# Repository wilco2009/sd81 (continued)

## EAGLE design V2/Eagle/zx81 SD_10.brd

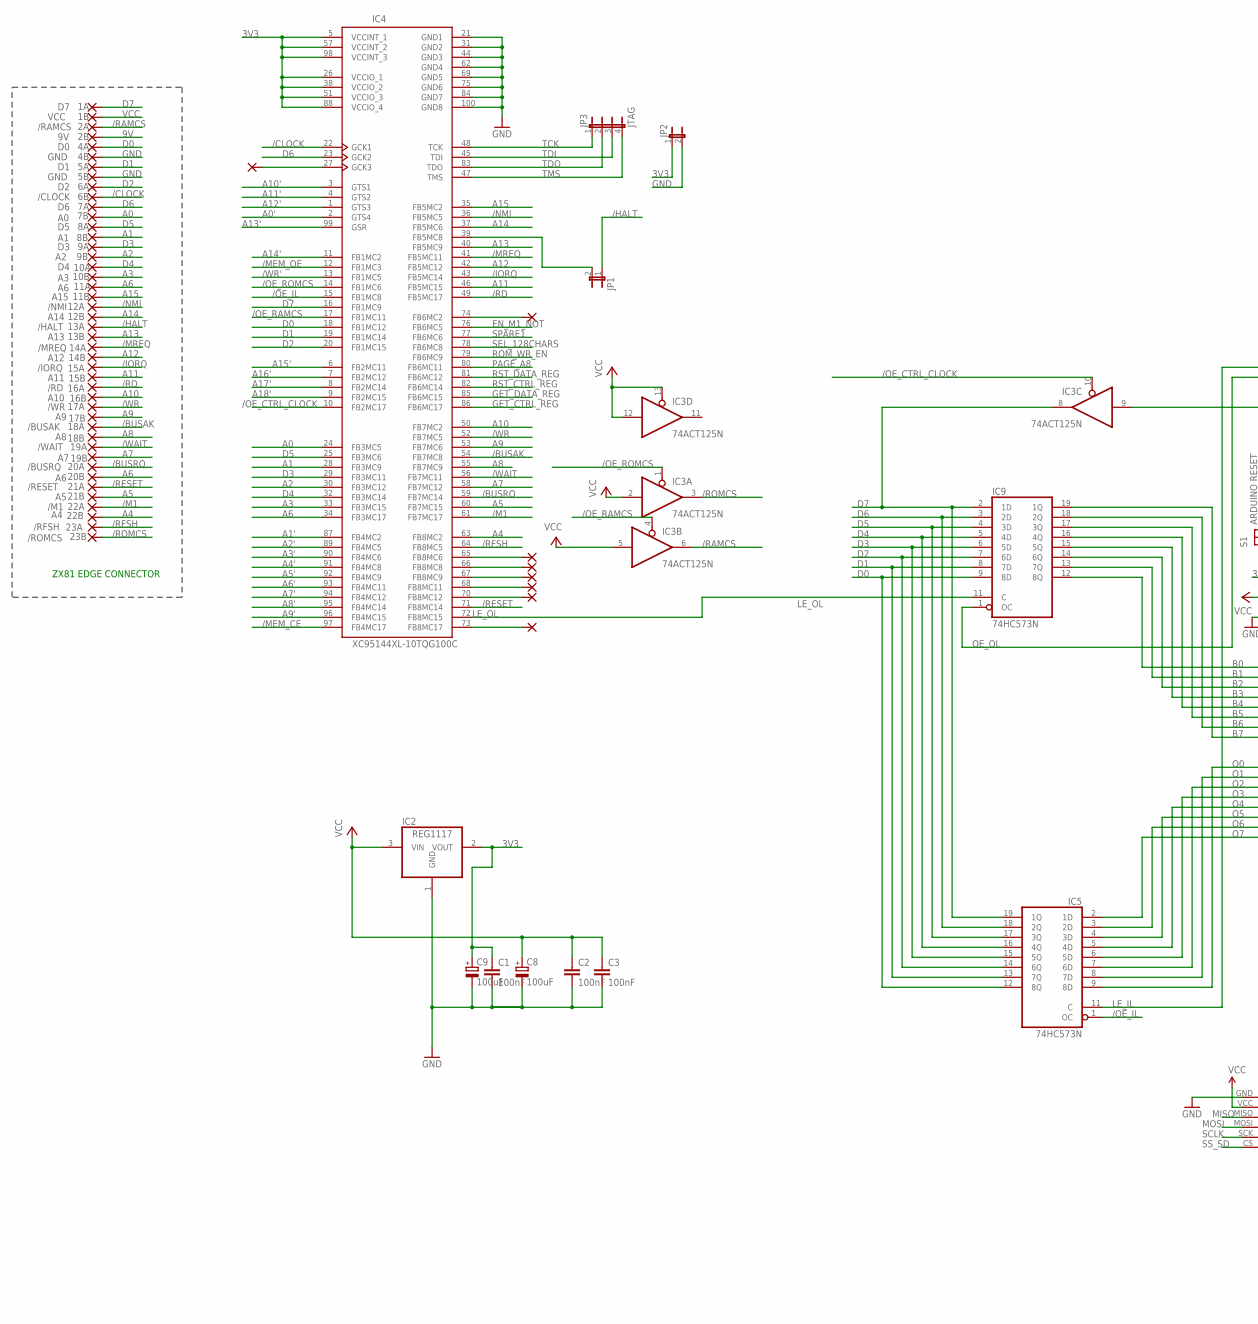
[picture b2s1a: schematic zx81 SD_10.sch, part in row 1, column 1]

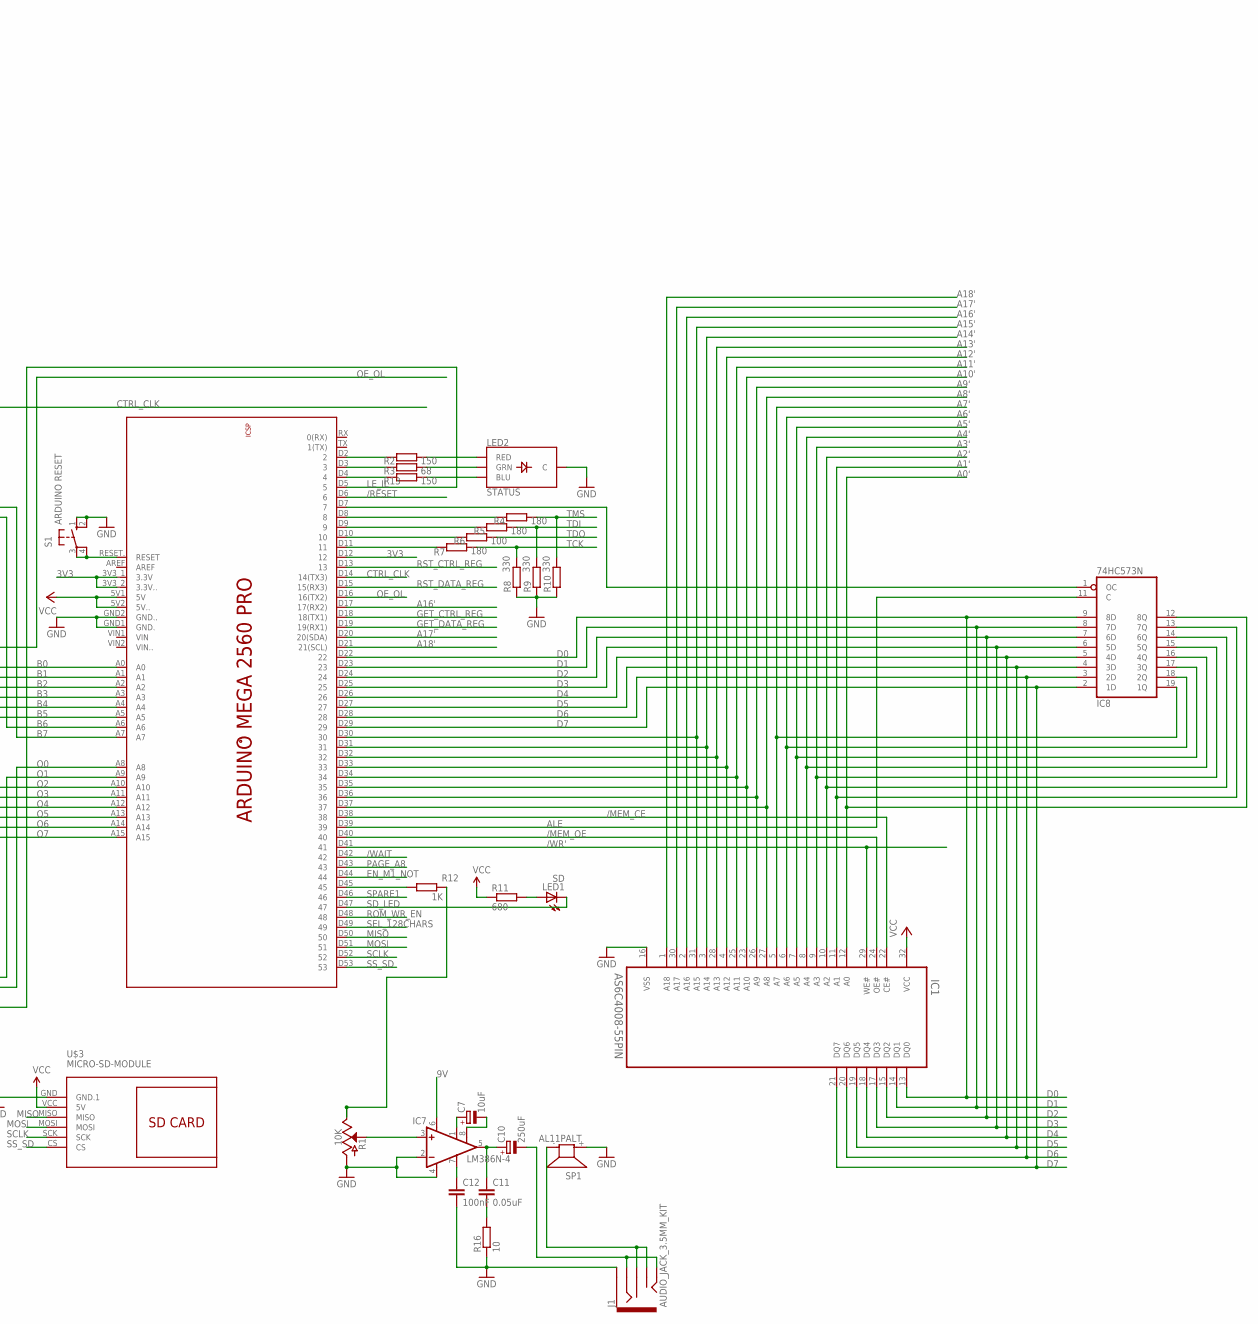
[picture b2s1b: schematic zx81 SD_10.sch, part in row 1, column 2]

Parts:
1A: D7; EDGEPIN
1B: VCC; EDGEPIN
2A: /RAMCS; EDGEPIN
2B: 9V; EDGEPIN
4A: D0; EDGEPIN
4B, 5B: GND; EDGEPIN
5A: D1; EDGEPIN
6A: D2; EDGEPIN
6B: /CLOCK; EDGEPIN
7A: D6; EDGEPIN
7B: A0; EDGEPIN
8A: D5; EDGEPIN
8B: A1; EDGEPIN
9A: D3; EDGEPIN
9B: A2; EDGEPIN
10A: D4; EDGEPIN
10B: A3; EDGEPIN
11A, 20B: A6; EDGEPIN
11B: A15; EDGEPIN
12A: /NMI; EDGEPIN
12B: A14; EDGEPIN
13A: /HALT; EDGEPIN
13B: A13; EDGEPIN
14A: /MREQ; EDGEPIN
14B: A12; EDGEPIN
15A: /IORQ; EDGEPIN
15B: A11; EDGEPIN
16A: /RD; EDGEPIN
16B: A10; EDGEPIN
17A: /WR; EDGEPIN
17B: A9; EDGEPIN
18A: /BUSAK; EDGEPIN
18B: A8; EDGEPIN
19A: /WAIT; EDGEPIN
19B: A7; EDGEPIN
20A: /BUSRQ; EDGEPIN
21A: /RESET; EDGEPIN
21B: A5; EDGEPIN
22A: /M1; EDGEPIN
22B: A4; EDGEPIN
23A: /RFSH; EDGEPIN
23B: /ROMCS; EDGEPIN
C1, C2, C3, C12: 100nF; C025-040X050
C7: 10uF; E2-5
C8, C9: 100uF; E2-5
C10: 250uF; E2-5
C11: 0.05uF; C025-040X050
IC1: AS6C4008-55PIN; DIP1524W45P254L4203H406Q32
IC2: REG1117; SOT223
IC3: 74ACT125N; DIL14
IC4: XC95144XL-10TQG100C; TQFP100
IC5, IC8, IC9: 74HC573N; DIL20
IC7: LM386N-4; DIL08
J1: AUDIO_JACK_3.5MM_KIT; AUDIO-JACK-KIT
JP1, JP2: JP1E; JP1
JP3: JTAG; JP4
LED1: SD; LED5MM
LED2: STATUS; LED-RGB-THRU
PAD1, PAD2, PAD3, PAD4, PAD5, PAD6, PAD7, PAD8: 1,6/0,8
R1: 10K; POT-WHEEL
R2, R13: 150; 0204/7
R3: 68; 0204/7
R4, R5, R7: 180; 0204/7
R6: 100; 0204/7
R8, R9, R10: 330; 0204/7
R11: 680; 0204/7
R12: 1K; 0204/7
R16: 10; 0204/7
S1: ARDUINO RESET; B3F-10XX
SP1: AL11PALT; ALT
U$2: ARDUINO_MEGA2560_PRO
U$3: MICRO-SD-MODULE; MICROSD-MODULE

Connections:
3V3: C1.1, C9.+, IC2.2 (VOUT), IC4.5 (VCCINT_1), IC4.26 (VCCIO_1), IC4.38 (VCCIO_2), IC4.51 (VCCIO_3), IC4.57 (VCCINT_2), IC4.88 (VCCIO_4), IC4.98 (VCCINT_3), JP2.1, U$2.3V3_1 (3.3V), U$2.3V3_2 (3.3V..), U$2.D12 (12)
9V: 2B.1, IC7.6 (VS)
/BUSAK: 18A.1, IC4.54 (FB7MC8)
/BUSRQ: 20A.1, IC4.59 (FB7MC14)
/CLOCK: 6B.1, IC4.22 (GCK1)
/HALT: 13A.1, JP1.1
/IORQ: 15A.1, IC4.43 (FB5MC14)
/M1: 22A.1, IC4.61 (FB7MC17)
/MEM_CE: IC1.22 (CE#), IC4.97 (FB4MC17), U$2.D38 (38)
/MEM_OE: IC1.24 (OE#), IC4.12 (FB1MC3), U$2.D40 (40)
/MREQ: 14A.1, IC4.41 (FB5MC11)
/NMI: 12A.1, IC4.36 (FB5MC5)
/OE_CTRL_CLOCK: IC3.10 (OE), IC4.10 (FB2MC17)
/OE_IL: IC4.15 (FB1MC8), IC5.1 (OC)
/OE_RAMCS: IC3.4 (OE), IC4.17 (FB1MC11)
/OE_ROMCS: IC3.1 (OE), IC4.14 (FB1MC6)
/RAMCS: 2A.1, IC3.6 (O)
/RD: 16A.1, IC4.49 (FB5MC17)
/RESET: 21A.1, IC4.71 (FB8MC14), U$2.D6 (6)
/RFSH: 23A.1, IC4.64 (FB8MC5)
/ROMCS: 23B.1, IC3.3 (O)
/WAIT: 19A.1, IC4.56 (FB7MC11), U$2.D42 (42)
/WR: 17A.1, IC4.52 (FB7MC5)
/WR': IC1.29 (WE#), IC4.13 (FB1MC5), U$2.D41 (41)
A0: 7B.1, IC4.24 (FB3MC5)
A0': IC1.12 (A0), IC4.2 (GTS4), IC8.12 (8Q)
A1: 8B.1, IC4.28 (FB3MC9)
A1': IC1.11 (A1), IC4.87 (FB4MC2), IC8.13 (7Q)
A2: 9B.1, IC4.30 (FB3MC12)
A2': IC1.10 (A2), IC4.89 (FB4MC5), IC8.14 (6Q)
A3: 10B.1, IC4.33 (FB3MC15)
A3': IC1.9 (A3), IC4.90 (FB4MC6), IC8.15 (5Q)
A4: 22B.1, IC4.63 (FB8MC2)
A4': IC1.8 (A4), IC4.91 (FB4MC8), IC8.16 (4Q)
A5: 21B.1, IC4.60 (FB7MC15)
A5': IC1.7 (A5), IC4.92 (FB4MC9), IC8.17 (3Q)
A6: 11A.1, 20B.1, IC4.34 (FB3MC17)
A6': IC1.6 (A6), IC4.93 (FB4MC11), IC8.18 (2Q)
A7: 19B.1, IC4.58 (FB7MC12)
A7': IC1.5 (A7), IC4.94 (FB4MC12), IC8.19 (1Q)
A8: 18B.1, IC4.55 (FB7MC9)
A8': IC1.27 (A8), IC4.95 (FB4MC14), U$2.D37 (37)
A9: 17B.1, IC4.53 (FB7MC6)
A9': IC1.26 (A9), IC4.96 (FB4MC15), U$2.D36 (36)
A10: 16B.1, IC4.50 (FB7MC2)
A10': IC1.23 (A10), IC4.3 (GTS1), U$2.D35 (35)
A11: 15B.1, IC4.46 (FB5MC15)
A11': IC1.25 (A11), IC4.4 (GTS2), U$2.D34 (34)
A12: 14B.1, IC4.42 (FB5MC12)
A12': IC1.4 (A12), IC4.1 (GTS3), U$2.D33 (33)
A13: 13B.1, IC4.40 (FB5MC9)
A13': IC1.28 (A13), IC4.99 (GSR), U$2.D32 (32)
A14: 12B.1, IC4.37 (FB5MC6)
A14': IC1.3 (A14), IC4.11 (FB1MC2), U$2.D31 (31)
A15: 11B.1, IC4.35 (FB5MC2)
A15': IC1.31 (A15), IC4.6 (FB2MC11), U$2.D30 (30)
A16': IC1.2 (A16), IC4.7 (FB2MC12), U$2.D17 (17(RX2))
A17': IC1.30 (A17), IC4.8 (FB2MC14), U$2.D20 (20(SDA))
A18': IC1.1 (A18), IC4.9 (FB2MC15), U$2.D21 (21(SCL))
ALE: IC8.11 (C), U$2.D39 (39)
B0: IC9.19 (1Q), U$2.A7
B1: IC9.18 (2Q), U$2.A6
B2: IC9.17 (3Q), U$2.A5
B3: IC9.16 (4Q), U$2.A4
B4: IC9.15 (5Q), U$2.A3
B5: IC9.14 (6Q), U$2.A2
B6: IC9.13 (7Q), U$2.A1
B7: IC9.12 (8Q), U$2.A0
CTRL_CLK: IC3.9 (I), U$2.D14 (14(TX3))
D0: 4A.1, IC1.13 (DQ0), IC4.18 (FB1MC12), IC5.12 (8Q), IC8.9 (8D), IC9.9 (8D), U$2.D22 (22)
D1: 5A.1, IC1.14 (DQ1), IC4.19 (FB1MC14), IC5.13 (7Q), IC8.8 (7D), IC9.8 (7D), U$2.D23 (23)
D2: 6A.1, IC1.15 (DQ2), IC4.20 (FB1MC15), IC5.14 (6Q), IC8.7 (6D), IC9.7 (6D), U$2.D24 (24)
D3: 9A.1, IC1.17 (DQ3), IC4.29 (FB3MC11), IC5.15 (5Q), IC8.6 (5D), IC9.6 (5D), U$2.D25 (25)
D4: 10A.1, IC1.18 (DQ4), IC4.32 (FB3MC14), IC5.16 (4Q), IC8.5 (4D), IC9.5 (4D), U$2.D26 (26)
D5: 8A.1, IC1.19 (DQ5), IC4.25 (FB3MC6), IC5.17 (3Q), IC8.4 (3D), IC9.4 (3D), U$2.D27 (27)
D6: 7A.1, IC1.20 (DQ6), IC4.23 (GCK2), IC5.18 (2Q), IC8.3 (2D), IC9.3 (2D), U$2.D28 (28)
D7: 1A.1, IC1.21 (DQ7), IC3.8 (O), IC4.16 (FB1MC9), IC5.19 (1Q), IC8.2 (1D), IC9.2 (1D), U$2.D29 (29)
EN_M1_NOT: IC4.76 (FB6MC5), U$2.D44 (44)
GET_CTRL_REG: IC4.86 (FB6MC17), U$2.D18 (18(TX1))
GET_DATA_REG: IC4.85 (FB6MC15), U$2.D19 (19(RX1))
GND: 4B.1, 5B.1, C1.2, C2.2, C3.2, C8.-, C9.-, C12.2, IC1.16 (VSS), IC2.1 (GND), IC3.7 (GND), IC4.21 (GND1), IC4.31 (GND2), IC4.44 (GND3), IC4.62 (GND4), IC4.69 (GND5), IC4.75 (GND6), IC4.84 (GND7), IC4.100 (GND8), IC5.10 (GND), IC7.2 (-IN), IC7.4 (GND), IC8.10 (GND), IC9.10 (GND), J1.SLEEVE, JP2.2, LED2.2 (C), R1.P$1 (A), R8.1, R9.1, R10.1, R16.1, S1.1 (S), S1.2 (S1), SP1.+ (1), U$2.GND1 (GND.), U$2.GND2 (GND..), U$3.GND (GND.1)
LE_IL: IC5.11 (C), U$2.D5 (5)
LE_OL: IC4.72 (FB8MC15), IC9.11 (C)
MISO: U$2.D50 (50), U$3.MISO
MOSI: U$2.D51 (51), U$3.MOSI
unnamed: IC8.1 (OC), U$2.D7 (7)
unnamed: IC4.74 (FB6MC2), PAD8.1
unnamed: J1.RSH, J1.TSH, SP1.- (2)
unnamed: R4.1, U$2.D8 (8)
unnamed: C10.-, J1.RING, J1.TIP
unnamed: IC7.3 (+IN), R1.P$3 (S)
unnamed: R1.P$2 (E), R12.2
unnamed: R12.1, U$2.D45 (45)
unnamed: C7.+, IC7.1 (GAIN)
unnamed: IC4.65 (FB8MC6), PAD2.1
unnamed: R5.1, U$2.D9 (9)
unnamed: R6.1, U$2.D10 (10)
unnamed: R7.1, U$2.D11 (11)
unnamed: LED1.A, R11.2
unnamed: IC4.66 (FB8MC8), PAD3.1
unnamed: C7.-, IC7.8 (GAIN)
unnamed: C10.+, C11.1, IC7.5 (OUT)
unnamed: IC4.67 (FB8MC9), PAD4.1
unnamed: C12.1, IC7.7 (BYPASS)
unnamed: C11.2, R16.2
unnamed: IC4.68 (FB8MC11), PAD5.1
unnamed: IC4.73 (FB8MC17), PAD6.1
unnamed: IC4.27 (GCK3), PAD1.1
unnamed: IC4.70 (FB8MC12), PAD7.1
unnamed: LED2.1 (RED), R2.2
unnamed: LED2.4 (GRN), R3.2
unnamed: LED2.3 (BLU), R13.2
unnamed: R2.1, U$2.D2 (2)
unnamed: R3.1, U$2.D3 (3)
unnamed: R13.1, U$2.D4 (4)
unnamed: S1.3, S1.4 (P1), U$2.RESET. (RESET)
unnamed: IC4.39 (FB5MC8), JP1.2
O0: IC5.2 (1D), U$2.A15
O1: IC5.3 (2D), U$2.A14
O2: IC5.4 (3D), U$2.A13
O3: IC5.5 (4D), U$2.A12
O4: IC5.6 (5D), U$2.A11
O5: IC5.7 (6D), U$2.A10
O6: IC5.8 (7D), U$2.A9
O7: IC5.9 (8D), U$2.A8
OE_OL: IC9.1 (OC), U$2.D16 (16(TX2))
PAGE_A8: IC4.80 (FB6MC11), U$2.D43 (43)
ROM_WR_EN: IC4.79 (FB6MC9), U$2.D48 (48)
RST_CTRL_REG: IC4.82 (FB6MC14), U$2.D13 (13)
RST_DATA_REG: IC4.81 (FB6MC12), U$2.D15 (15(RX3))
SCLK: U$2.D52 (52), U$3.SCK
SD_LED: LED1.K (C), U$2.D47 (47)
SEL_128CHARS: IC4.78 (FB6MC8), U$2.D49 (49)
SPARE1: IC4.77 (FB6MC6), U$2.D46 (46)
SS_SD: U$2.D53 (53), U$3.CS
TCK: IC4.48 (TCK), JP3.1, R7.2, R8.2
TDI: IC4.45 (TDI), JP3.3, R5.2, R9.2
TDO: IC4.83 (TDO), JP3.2, R6.2
TMS: IC4.47 (TMS), JP3.4, R4.2, R10.2
VCC: 1B.1, C2.1, C3.1, C8.+, IC1.32 (VCC), IC2.3 (VIN), IC3.2 (I), IC3.5 (I), IC3.12 (I), IC3.13 (OE), IC3.14 (VCC), IC5.20 (VCC), IC8.20 (VCC), IC9.20 (VCC), R11.1, U$2.5V1 (5V), U$2.5V2 (5V..), U$3.VCC (5V)

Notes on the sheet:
ZX81 EDGE CONNECTOR

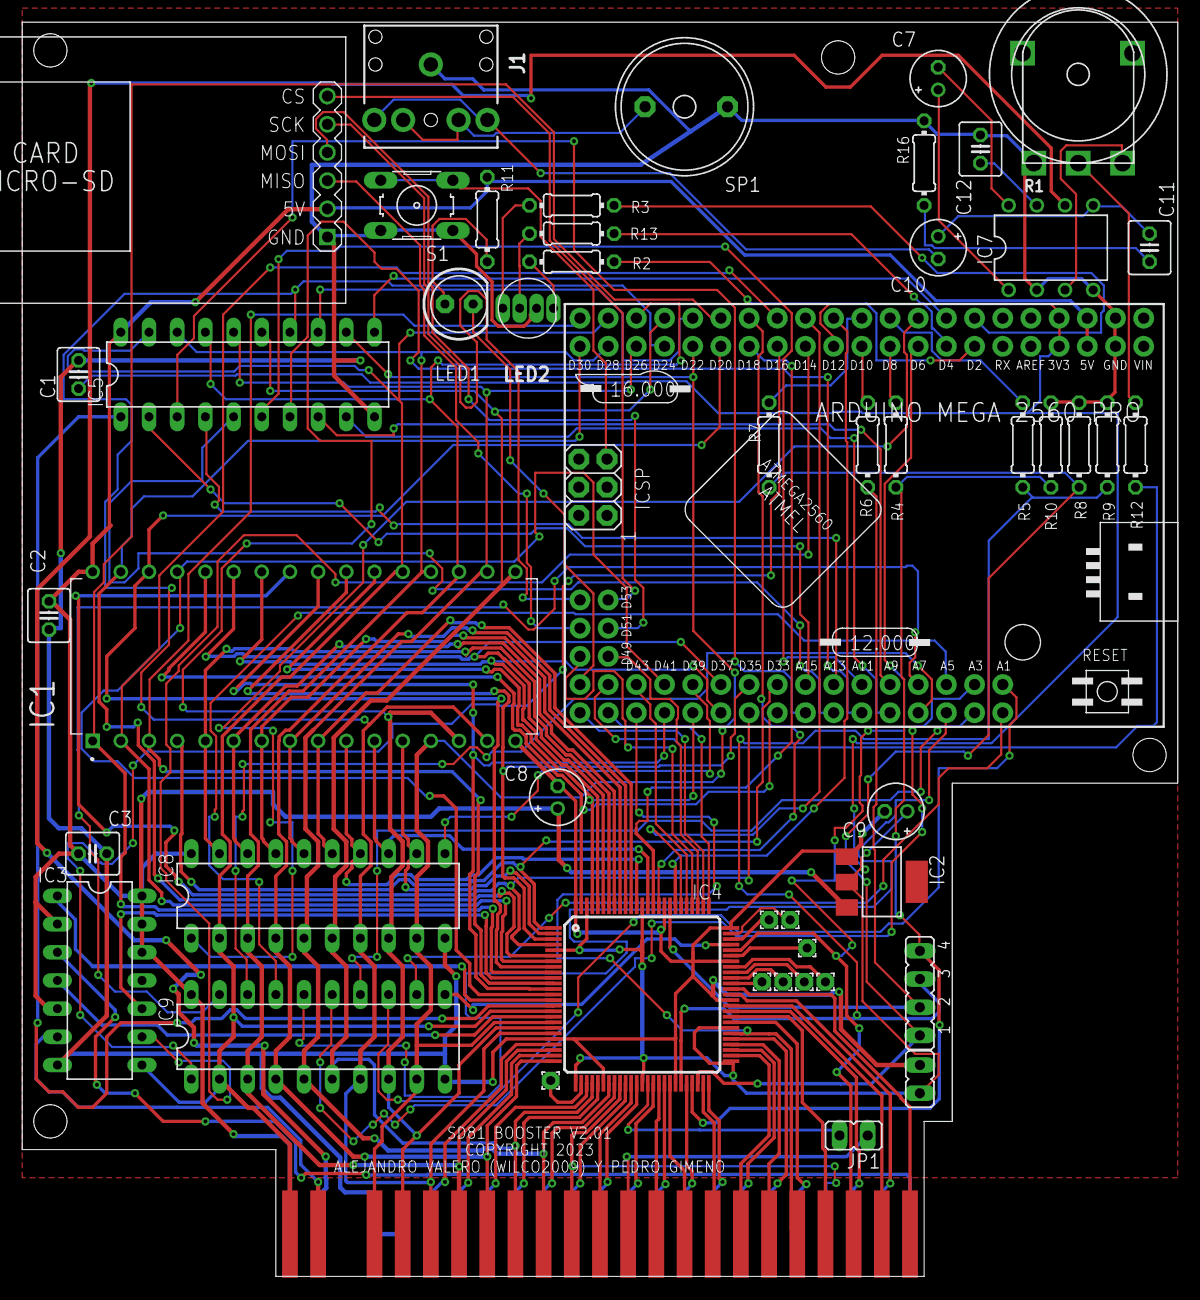
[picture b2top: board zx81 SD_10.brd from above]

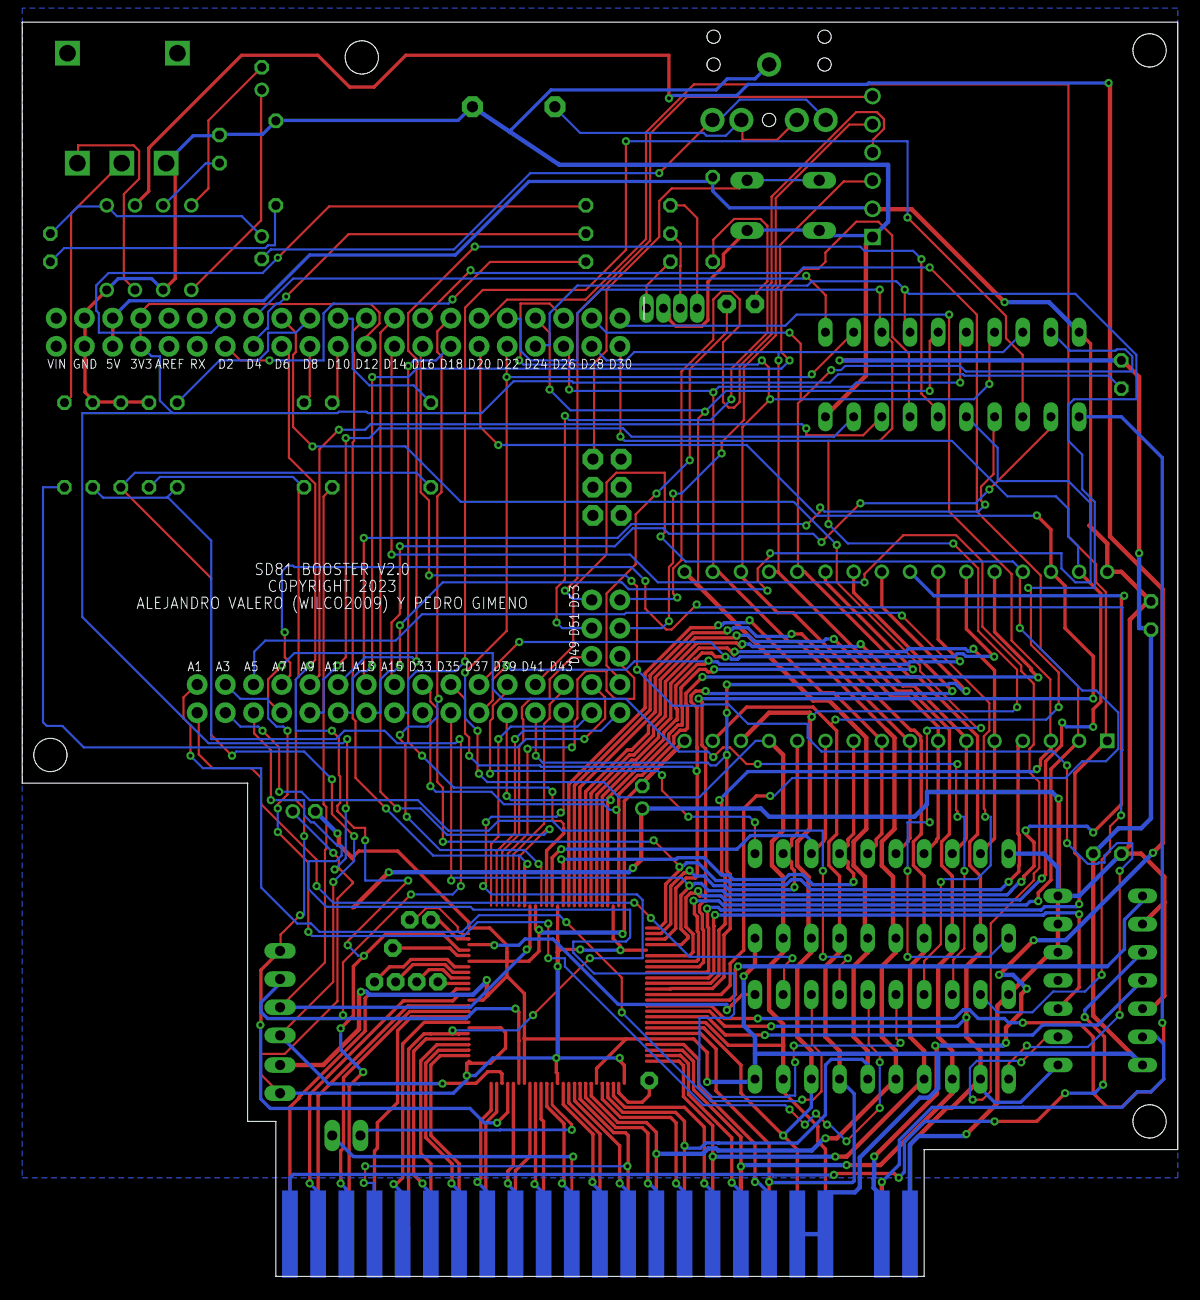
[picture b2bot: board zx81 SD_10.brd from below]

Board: 2 copper layers, 104.1 x 113.0 mm, 93 parts (22 on the bottom side), 140 nets.

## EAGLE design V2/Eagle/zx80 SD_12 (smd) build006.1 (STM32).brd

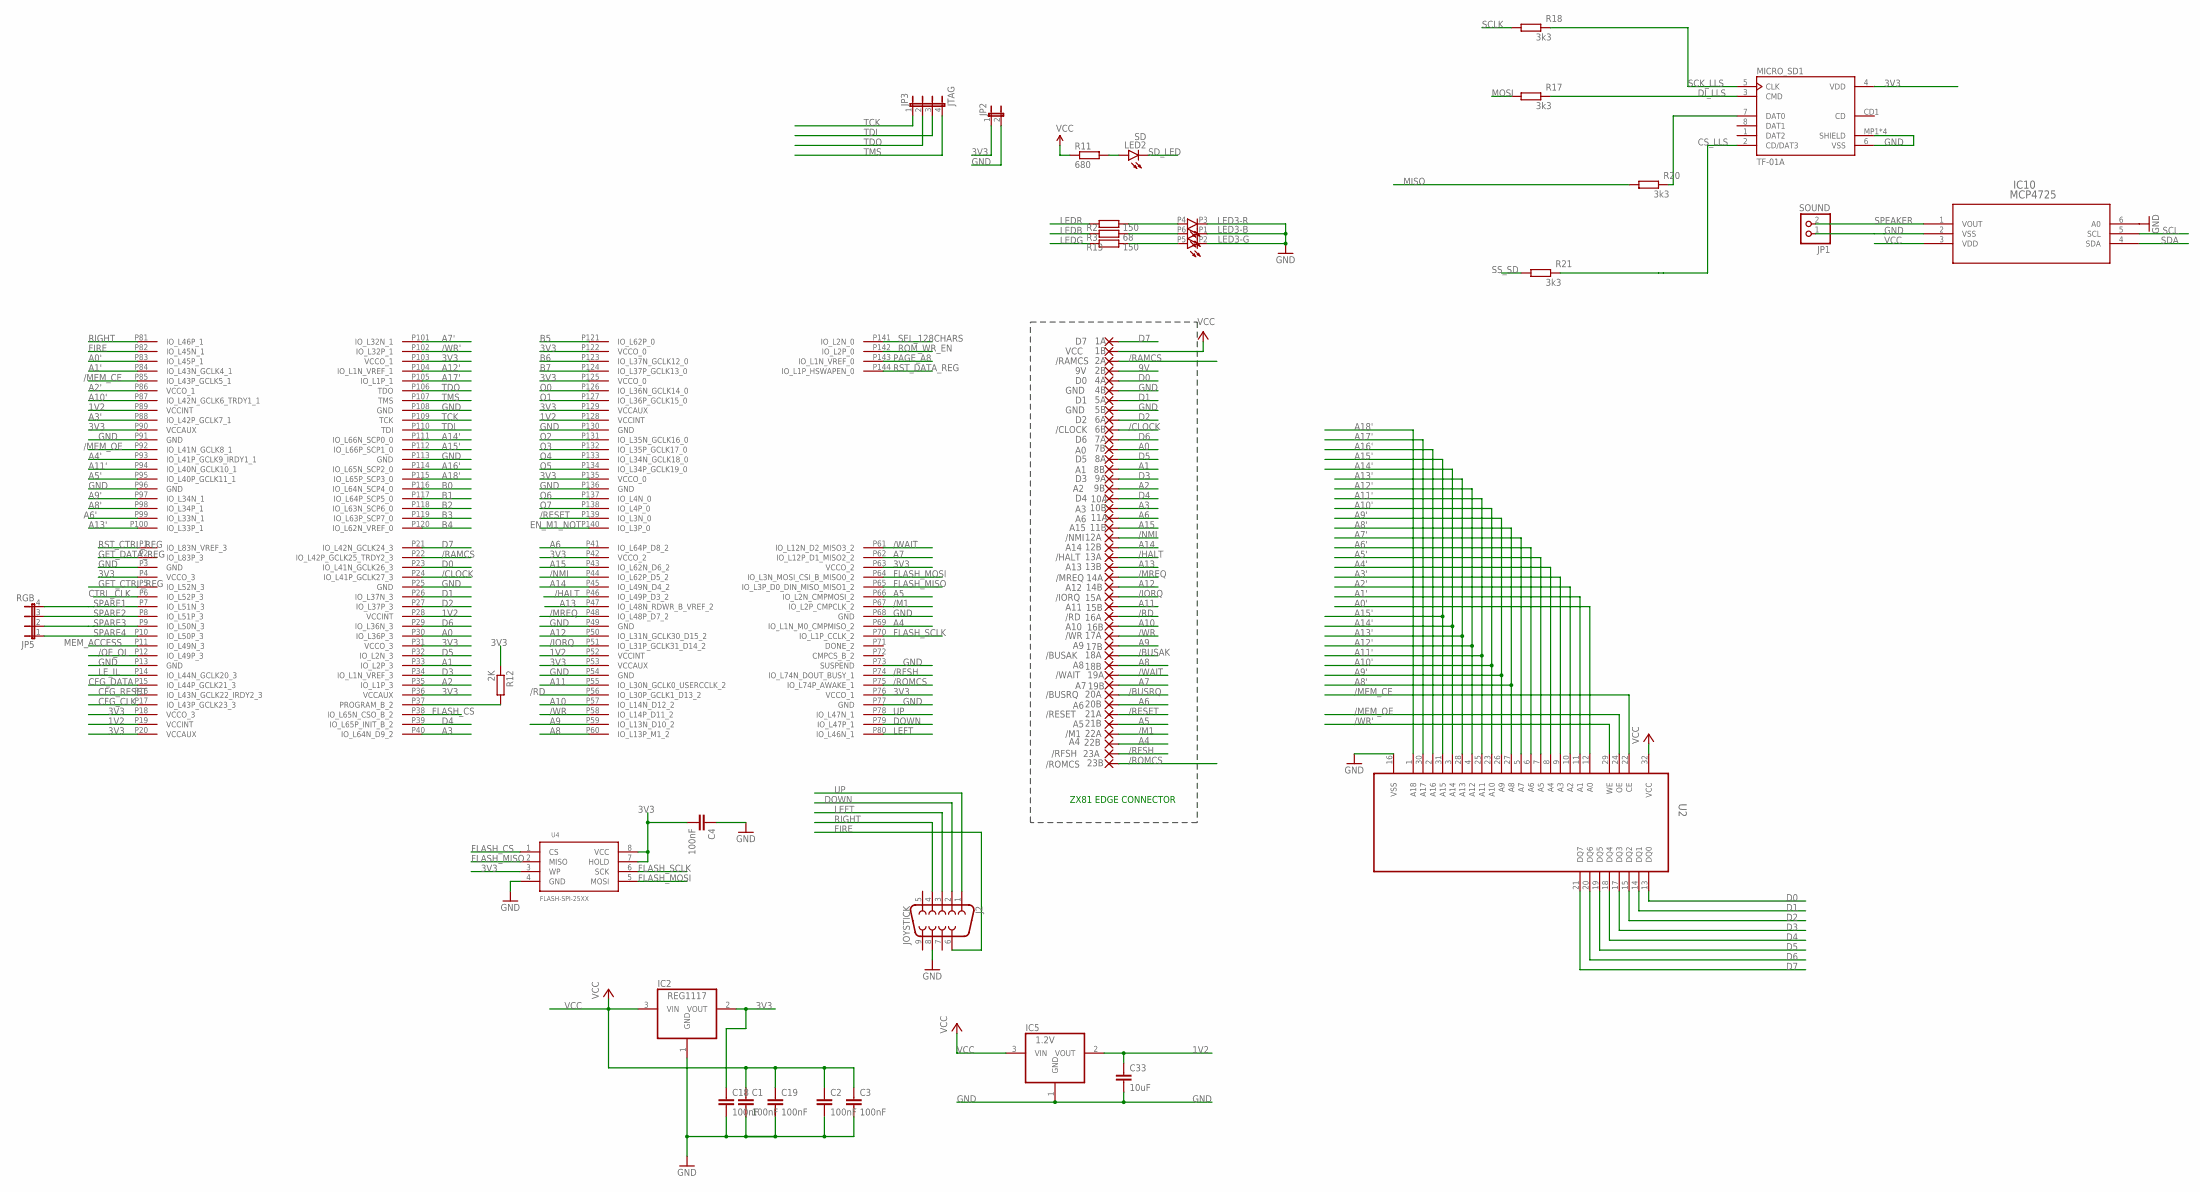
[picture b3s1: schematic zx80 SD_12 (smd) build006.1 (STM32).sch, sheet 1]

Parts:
1A: D7; EDGEPIN
1B: VCC; EDGEPIN
2A: /RAMCS; EDGEPIN
2B: 9V; EDGEPIN
4A: D0; EDGEPIN
4B, 5B: GND; EDGEPIN
5A: D1; EDGEPIN
6A: D2; EDGEPIN
6B: /CLOCK; EDGEPIN
7A: D6; EDGEPIN
7B: A0; EDGEPIN
8A: D5; EDGEPIN
8B: A1; EDGEPIN
9A: D3; EDGEPIN
9B: A2; EDGEPIN
10A: D4; EDGEPIN
10B: A3; EDGEPIN
11A, 20B: A6; EDGEPIN
11B: A15; EDGEPIN
12A: /NMI; EDGEPIN
12B: A14; EDGEPIN
13A: /HALT; EDGEPIN
13B: A13; EDGEPIN
14A: /MREQ; EDGEPIN
14B: A12; EDGEPIN
15A: /IORQ; EDGEPIN
15B: A11; EDGEPIN
16A: /RD; EDGEPIN
16B: A10; EDGEPIN
17A: /WR; EDGEPIN
17B: A9; EDGEPIN
18A: /BUSAK; EDGEPIN
18B: A8; EDGEPIN
19A: /WAIT; EDGEPIN
19B: A7; EDGEPIN
20A: /BUSRQ; EDGEPIN
21A: /RESET; EDGEPIN
21B: A5; EDGEPIN
22A: /M1; EDGEPIN
22B: A4; EDGEPIN
23A: /RFSH; EDGEPIN
23B: /ROMCS; EDGEPIN
C1, C2, C3, C18, C19: 100nF; C0603
C4: 100nF; C0603K
C33: 10uF; C0603K
IC2: REG1117; SOT223
IC5: 1.2V; SOT223
IC10: MCP4725; SOT-23-6_MC
J2: JOYSTICK; DB9_MALE
JP1: SOUND; 1X02
JP2: JP1E; JP1
JP3: JTAG; JP4
JP5: RGB; JP4
LED2: SD; CHIPLED_0603
LED3: STATUS; 3535-PLCC6
MICRO_SD1: TF-01A
R2, R13: 150; R0603
R3: 68; R0603
R11: 680; R0603
R12: 2K; R0603
R17, R18, R20, R21: 3k3; R0603
U2: AS6C4008; SOP32-5
U4: FLASH-SPI-25XX; SO08-EIAJ
U$1: XC6SLX9-2TQG144C; TQ144

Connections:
1V2: C33.1, IC5.2 (VOUT), U$1.P19 (VCCINT), U$1.P28 (VCCINT), U$1.P52 (VCCINT), U$1.P89 (VCCINT), U$1.P128 (VCCINT)
3V3: C4.2, C18.1, IC2.2 (VOUT), JP2.1, MICRO_SD1.4 (VDD), R12.1, U4.3 (WP), U4.7 (HOLD), U4.8 (VCC), U$1.P4 (VCCO_3), U$1.P18 (VCCO_3), U$1.P20 (VCCAUX), U$1.P31 (VCCO_3), U$1.P36 (VCCAUX), U$1.P42 (VCCO_2), U$1.P53 (VCCAUX), U$1.P63 (VCCO_2), U$1.P76 (VCCO_1), U$1.P90 (VCCAUX), U$1.P103 (VCCO_1), U$1.P122 (VCCO_0), U$1.P125 (VCCO_0), U$1.P129 (VCCAUX), U$1.P135 (VCCO_0); also elsewhere on the board
9V: 2B.1
/BUSAK: 18A.1
/BUSRQ: 20A.1
/CLOCK: 6B.1, U$1.P24 (IO_L41P_GCLK27_3)
/HALT: 13A.1, U$1.P46 (IO_L49P_D3_2)
/IORQ: 15A.1, U$1.P51 (IO_L31P_GCLK31_D14_2)
/M1: 22A.1, U$1.P67 (IO_L2P_CMPCLK_2)
/MEM_CE: U2.22 (CE), U$1.P85 (IO_L43P_GCLK5_1)
/MEM_OE: U2.24 (OE), U$1.P92 (IO_L41N_GCLK8_1)
/MREQ: 14A.1, U$1.P48 (IO_L48P_D7_2)
/NMI: 12A.1, U$1.P44 (IO_L62P_D5_2)
/OE_OL: U$1.P12 (IO_L49P_3); also elsewhere on the board
/RAMCS: 2A.1, U$1.P22 (IO_L42P_GCLK25_TRDY2_3)
/RD: 16A.1, U$1.P56 (IO_L30P_GCLK1_D13_2)
/RESET: 21A.1, U$1.P139 (IO_L3N_0); also elsewhere on the board
/RFSH: 23A.1, U$1.P74 (IO_L74N_DOUT_BUSY_1)
/ROMCS: 23B.1, U$1.P75 (IO_L74P_AWAKE_1)
/WAIT: 19A.1, U$1.P61 (IO_L12N_D2_MISO3_2); also elsewhere on the board
/WR: 17A.1, U$1.P58 (IO_L14P_D11_2); also elsewhere on the board
/WR': U2.29 (WE), U$1.P102 (IO_L32P_1)
A0: 7B.1, U$1.P30 (IO_L36P_3)
A0': U2.12 (A0), U$1.P83 (IO_L45P_1); also elsewhere on the board
A1: 8B.1, U$1.P33 (IO_L2P_3)
A1': U2.11 (A1), U$1.P84 (IO_L43N_GCLK4_1); also elsewhere on the board
A2: 9B.1, U$1.P35 (IO_L1P_3)
A2': U2.10 (A2), U$1.P86 (VCCO_1); also elsewhere on the board
A3: 10B.1, U$1.P40 (IO_L64N_D9_2)
A3': U2.9 (A3), U$1.P88 (IO_L42P_GCLK7_1); also elsewhere on the board
A4: 22B.1, U$1.P69 (IO_L1N_M0_CMPMISO_2)
A4': U2.8 (A4), U$1.P93 (IO_L41P_GCLK9_IRDY1_1); also elsewhere on the board
A5: 21B.1, U$1.P66 (IO_L2N_CMPMOSI_2)
A5': U2.7 (A5), U$1.P95 (IO_L40P_GCLK11_1); also elsewhere on the board
A6: 11A.1, 20B.1, U$1.P41 (IO_L64P_D8_2)
A6': U2.6 (A6), U$1.P99 (IO_L33N_1); also elsewhere on the board
A7: 19B.1, U$1.P62 (IO_L12P_D1_MISO2_2)
A7': U2.5 (A7), U$1.P101 (IO_L32N_1); also elsewhere on the board
A8: 18B.1, U$1.P60 (IO_L13P_M1_2)
A8': U2.27 (A8), U$1.P98 (IO_L34P_1); also elsewhere on the board
A9: 17B.1, U$1.P59 (IO_L13N_D10_2)
A9': U2.26 (A9), U$1.P97 (IO_L34N_1); also elsewhere on the board
A10: 16B.1, U$1.P57 (IO_L14N_D12_2)
A10': U2.23 (A10), U$1.P87 (IO_L42N_GCLK6_TRDY1_1); also elsewhere on the board
A11: 15B.1, U$1.P55 (IO_L30N_GCLK0_USERCCLK_2)
A11': U2.25 (A11), U$1.P94 (IO_L40N_GCLK10_1); also elsewhere on the board
A12: 14B.1, U$1.P50 (IO_L31N_GCLK30_D15_2)
A12': U2.4 (A12), U$1.P104 (IO_L1N_VREF_1); also elsewhere on the board
A13: 13B.1, U$1.P47 (IO_L48N_RDWR_B_VREF_2)
A13': U2.28 (A13), U$1.P100 (IO_L33P_1); also elsewhere on the board
A14: 12B.1, U$1.P45 (IO_L49N_D4_2)
A14': U2.3 (A14), U$1.P111 (IO_L66N_SCP0_0); also elsewhere on the board
A15: 11B.1, U$1.P43 (IO_L62N_D6_2)
A15': U2.31 (A15), U$1.P112 (IO_L66P_SCP1_0); also elsewhere on the board
A16': U2.2 (A16), U$1.P114 (IO_L65N_SCP2_0); also elsewhere on the board
A17': U2.30 (A17), U$1.P105 (IO_L1P_1); also elsewhere on the board
A18': U2.1 (A18), U$1.P115 (IO_L65P_SCP3_0); also elsewhere on the board
B0: U$1.P116 (IO_L64N_SCP4_0); also elsewhere on the board
B1: U$1.P117 (IO_L64P_SCP5_0); also elsewhere on the board
B2: U$1.P118 (IO_L63N_SCP6_0); also elsewhere on the board
B3: U$1.P119 (IO_L63P_SCP7_0); also elsewhere on the board
B4: U$1.P120 (IO_L62N_VREF_0); also elsewhere on the board
B5: U$1.P121 (IO_L62P_0); also elsewhere on the board
B6: U$1.P123 (IO_L37N_GCLK12_0); also elsewhere on the board
B7: U$1.P124 (IO_L37P_GCLK13_0); also elsewhere on the board
CFG_CLK: U$1.P17 (IO_L43P_GCLK23_3); also elsewhere on the board
CFG_DATA: U$1.P15 (IO_L44P_GCLK21_3); also elsewhere on the board
CFG_RESET: U$1.P16 (IO_L43N_GCLK22_IRDY2_3); also elsewhere on the board
CS_LLS: MICRO_SD1.2 (CD/DAT3), R21.2
CTRL_CLK: U$1.P6 (IO_L52P_3); also elsewhere on the board
D0: 4A.1, U2.13 (DQ0), U$1.P23 (IO_L41N_GCLK26_3)
D1: 5A.1, U2.14 (DQ1), U$1.P26 (IO_L37N_3)
D2: 6A.1, U2.15 (DQ2), U$1.P27 (IO_L37P_3)
D3: 9A.1, U2.17 (DQ3), U$1.P34 (IO_L1N_VREF_3)
D4: 10A.1, U2.18 (DQ4), U$1.P39 (IO_L65P_INIT_B_2)
D5: 8A.1, U2.19 (DQ5), U$1.P32 (IO_L2N_3)
D6: 7A.1, U2.20 (DQ6), U$1.P29 (IO_L36N_3)
D7: 1A.1, U2.21 (DQ7), U$1.P21 (IO_L42N_GCLK24_3)
DI_LLS: MICRO_SD1.3 (CMD), R17.2
DOWN: J2.2, U$1.P79 (IO_L47P_1)
EN_M1_NOT: U$1.P140 (IO_L3P_0); also elsewhere on the board
FIRE: J2.6, U$1.P82 (IO_L45N_1)
FLASH_CS: U4.1 (CS), U$1.P38 (IO_L65N_CSO_B_2)
FLASH_MISO: U4.2 (MISO), U$1.P65 (IO_L3P_D0_DIN_MISO_MISO1_2)
FLASH_MOSI: U4.5 (MOSI), U$1.P64 (IO_L3N_MOSI_CSI_B_MISO0_2)
FLASH_SCLK: U4.6 (SCK), U$1.P70 (IO_L1P_CCLK_2)
GET_CTRL_REG: U$1.P5 (IO_L52N_3); also elsewhere on the board
GET_DATA_REG: U$1.P2 (IO_L83P_3); also elsewhere on the board
GND: 4B.1, 5B.1, C1.2, C2.2, C3.2, C4.1, C18.2, C19.2, C33.2, IC2.1 (GND), IC5.1 (GND), IC10.2 (VSS), IC10.6 (A0), J2.8, JP1.1, JP2.2, LED3.P1 (C), LED3.P2 (C), LED3.P3 (C), MICRO_SD1.6 (VSS), MICRO_SD1.MP1 (SHIELD), MICRO_SD1.MP2 (SHIELD), MICRO_SD1.MP3 (SHIELD), MICRO_SD1.MP4 (SHIELD), U2.16 (VSS), U4.4 (GND), U$1.P3 (GND), U$1.P13 (GND), U$1.P25 (GND), U$1.P49 (GND), U$1.P54 (GND), U$1.P68 (GND), U$1.P73 (SUSPEND), U$1.P77 (GND), U$1.P91 (GND), U$1.P96 (GND), U$1.P108 (GND), U$1.P113 (GND), U$1.P130 (GND), U$1.P136 (GND); also elsewhere on the board
LEDB: R3.1; also elsewhere on the board
LEDG: R13.1; also elsewhere on the board
LEDR: R2.1; also elsewhere on the board
LEFT: J2.3, U$1.P80 (IO_L46N_1)
LE_IL: U$1.P14 (IO_L44N_GCLK20_3); also elsewhere on the board
MEM_ACCESS: U$1.P11 (IO_L49N_3); also elsewhere on the board
MISO: R20.1; also elsewhere on the board
MOSI: R17.1; also elsewhere on the board
unnamed: MICRO_SD1.7 (DAT0), R20.2
unnamed: R12.2, U$1.P37 (PROGRAM_B_2)
unnamed: LED2.A, R11.2
unnamed: LED3.P4 (A), R2.2
unnamed: LED3.P6 (A), R3.2
unnamed: LED3.P5 (A), R13.2
O0: U$1.P126 (IO_L36N_GCLK14_0); also elsewhere on the board
O1: U$1.P127 (IO_L36P_GCLK15_0); also elsewhere on the board
O2: U$1.P131 (IO_L35N_GCLK16_0); also elsewhere on the board
O3: U$1.P132 (IO_L35P_GCLK17_0); also elsewhere on the board
O4: U$1.P133 (IO_L34N_GCLK18_0); also elsewhere on the board
O5: U$1.P134 (IO_L34P_GCLK19_0); also elsewhere on the board
O6: U$1.P137 (IO_L4N_0); also elsewhere on the board
O7: U$1.P138 (IO_L4P_0); also elsewhere on the board
PAGE_A8: U$1.P143 (IO_L1N_VREF_0); also elsewhere on the board
RIGHT: J2.4, U$1.P81 (IO_L46P_1)
ROM_WR_EN: U$1.P142 (IO_L2P_0); also elsewhere on the board
RST_CTRL_REG: U$1.P1 (IO_L83N_VREF_3); also elsewhere on the board
RST_DATA_REG: U$1.P144 (IO_L1P_HSWAPEN_0); also elsewhere on the board
SCK_LLS: MICRO_SD1.5 (CLK), R18.2
SCL: IC10.5 (SCL); also elsewhere on the board
SCLK: R18.1; also elsewhere on the board
SDA: IC10.4 (SDA); also elsewhere on the board
SD_LED: LED2.C; also elsewhere on the board
SEL_128CHARS: U$1.P141 (IO_L2N_0); also elsewhere on the board
SPARE1: JP5.4, U$1.P7 (IO_L51N_3); also elsewhere on the board
SPARE2: JP5.3, U$1.P8 (IO_L51P_3); also elsewhere on the board
SPARE3: JP5.2, U$1.P9 (IO_L50N_3); also elsewhere on the board
SPARE4: JP5.1, U$1.P10 (IO_L50P_3); also elsewhere on the board
SPEAKER: IC10.1 (VOUT), JP1.2
SS_SD: R21.1; also elsewhere on the board
TCK: JP3.1, U$1.P109 (TCK)
TDI: JP3.3, U$1.P110 (TDI)
TDO: JP3.2, U$1.P106 (TDO)
TMS: JP3.4, U$1.P107 (TMS)
UP: J2.1, U$1.P78 (IO_L47N_1)
VCC: 1B.1, C1.1, C2.1, C3.1, C19.1, IC2.3 (VIN), IC5.3 (VIN), IC10.3 (VDD), R11.1, U2.32 (VCC); also elsewhere on the board

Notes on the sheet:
ZX81 EDGE CONNECTOR
